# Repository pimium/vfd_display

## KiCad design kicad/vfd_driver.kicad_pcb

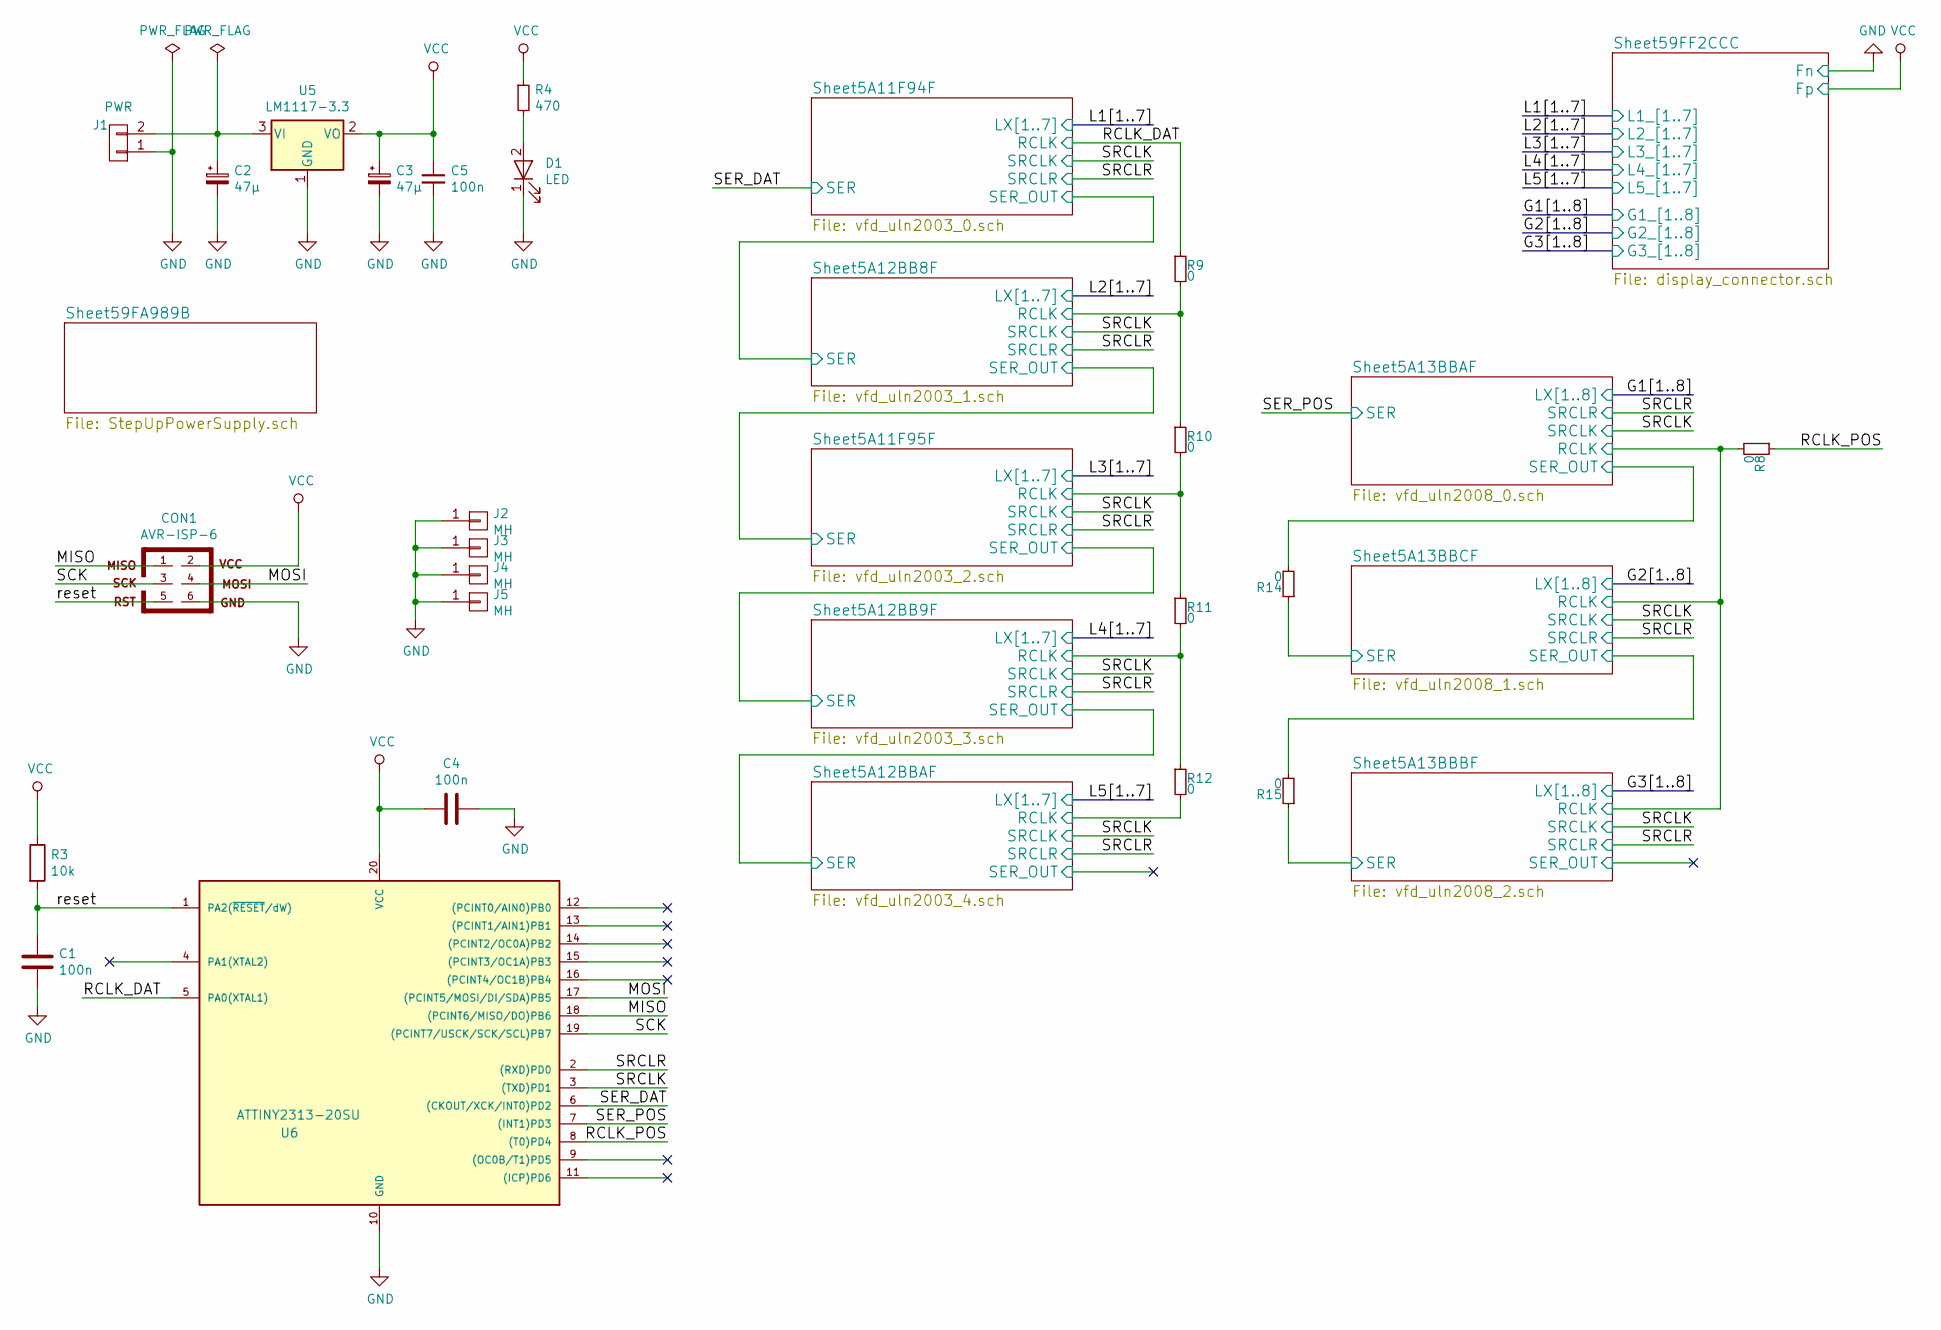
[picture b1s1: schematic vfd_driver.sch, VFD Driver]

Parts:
C1, C4, C5: 100n; C_0805_HandSoldering
C2, C3: 47µ; CP_Radial_Tantal_D4.5mm_P2.50mm
CON1: AVR-ISP-6; Pin_Header_Straight_2x03_Pitch2.54mm_SMD
D1: LED; LED_0805
J1: PWR; PINHEAD1-2
J2, J3, J4, J5: MH; MountingHole_3.2mm_M3_DIN965_Pad
R3: 10k; R_1206
R4: 470; R_1206
R8, R9, R10, R11, R12, R14, R15: 0; R_1206
U5: LM1117-3.3; SOT-223_pin4_3
U6: ATTINY2313-20SU; SOIC-20W_7.5x12.8mm_Pitch1.27mm

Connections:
/MISO: CON1.1, U6.18 ((PCINT6/MISO/DO)PB6)
/MOSI: CON1.4, U6.17 ((PCINT5/MOSI/DI/SDA)PB5)
/RCLK_0: R8.1, U6.8 ((T0)PD4)
/RCLK_7: R9.1, U6.5 (PA0(XTAL1)); also elsewhere on the board
/SCK: CON1.3, U6.19 ((PCINT7/USCK/SCK/SCL)PB7)
/SER_DAT: U6.6 ((CKOUT/XCK/INT0)PD2); also elsewhere on the board
/SER_POS: U6.7 ((INT1)PD3); also elsewhere on the board
/SRCLK: U6.3 ((TXD)PD1); also elsewhere on the board
/SRCLR: U6.2 ((RXD)PD0); also elsewhere on the board
/Sheet5A11F95F/RCLK: R10.2, R11.1; also elsewhere on the board
/Sheet5A12BB8F/RCLK: R9.2, R10.1; also elsewhere on the board
/Sheet5A12BB9F/RCLK: R11.2, R12.1; also elsewhere on the board
/Sheet5A12BBAF/RCLK: R12.2; also elsewhere on the board
/Sheet5A13BBAF/RCLK: R8.2; also elsewhere on the board
/Sheet5A13BBAF/SER_OUT: R14.2; also elsewhere on the board
/Sheet5A13BBBF/SER: R15.1; also elsewhere on the board
/Sheet5A13BBCF/SER: R14.1; also elsewhere on the board
/Sheet5A13BBCF/SER_OUT: R15.2; also elsewhere on the board
/reset: C1.1, CON1.5, R3.2, U6.1 (PA2(~RESET~/dW))
GND: C1.2, C2.2, C3.2, C4.1, C5.2, CON1.6, D1.1 (K), J1.1, J2.1, J3.1, J4.1, J5.1, U5.1 (GND), U6.10 (GND); also elsewhere on the board
unnamed: C2.1, J1.2, U5.3 (VI)
unnamed: D1.2 (A), R4.2
VCC: C3.1, C4.2, C5.1, CON1.2, R3.1, R4.1, U5.2 (VO), U6.20 (VCC); also elsewhere on the board

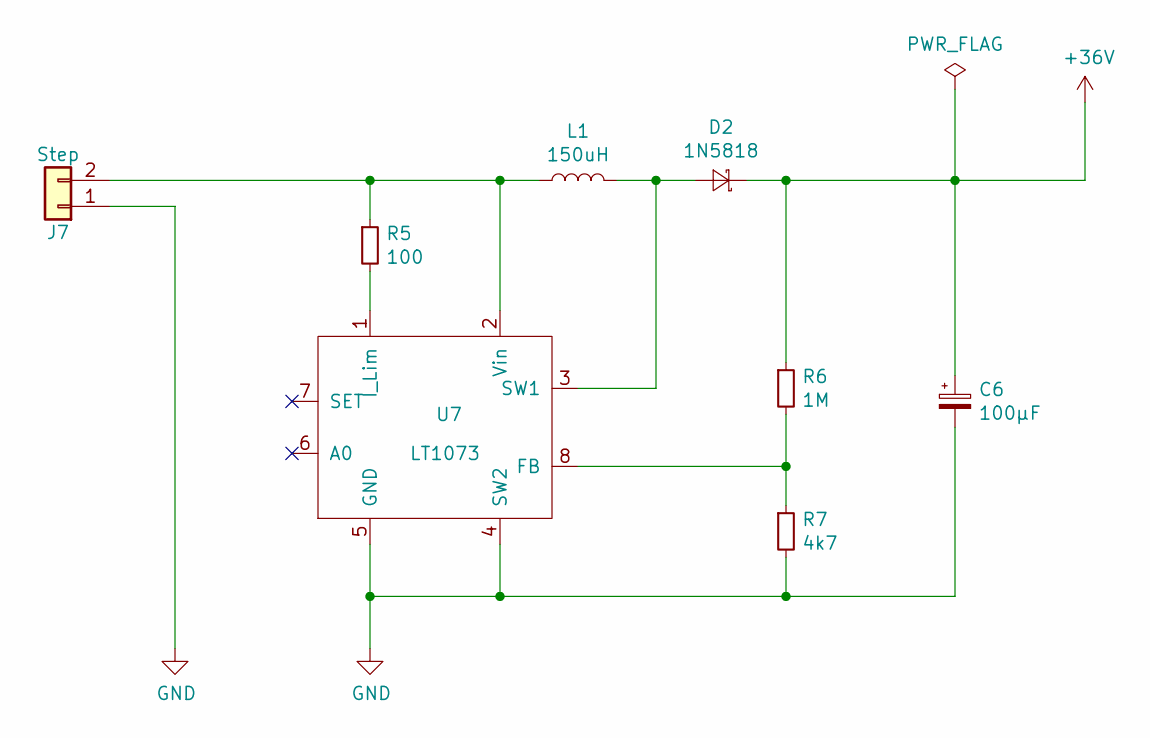
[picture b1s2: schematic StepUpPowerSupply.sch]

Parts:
C6: 100µF; CP_Elec_8x5.4
D2: 1N5818; D_SMA_Handsoldering
J7: Step; PINHEAD1-2
L1: 150uH; Choke_CD75
R5: 100; R_1206
R6: 1M; R_1206
R7: 4k7; R_1206
U7: LT1073; SOIC-8_3.9x4.9mm_Pitch1.27mm

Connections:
+36V: C6.1, D2.1 (K), R6.1; also elsewhere on the board
GND: C6.2, J7.1, R7.2, U7.4 (SW2), U7.5 (GND); also elsewhere on the board
unnamed: D2.2 (A), L1.2, U7.3 (SW1)
unnamed: J7.2, L1.1, R5.1, U7.2 (Vin)
unnamed: R5.2, U7.1 (I_Lim)
unnamed: R6.2, R7.1, U7.8 (FB)

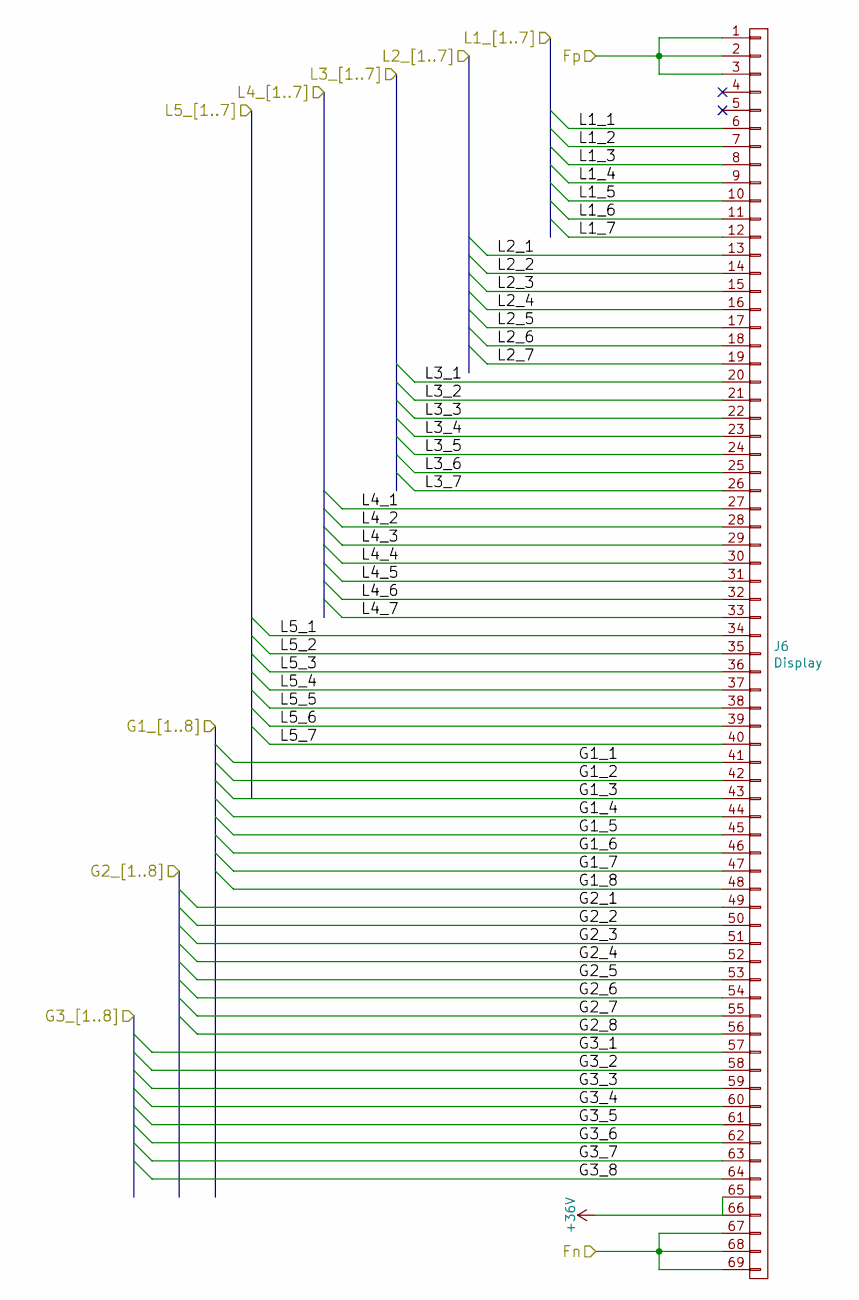
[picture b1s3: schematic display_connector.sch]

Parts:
J6: Display; vfd_FUTABA_24-SD-01GK_24x1

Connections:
+36V: J6.65, J6.66; also elsewhere on the board
/Sheet59FF2CCC/G1_1: J6.41; also elsewhere on the board
/Sheet59FF2CCC/G1_2: J6.42; also elsewhere on the board
/Sheet59FF2CCC/G1_3: J6.43; also elsewhere on the board
/Sheet59FF2CCC/G1_4: J6.44; also elsewhere on the board
/Sheet59FF2CCC/G1_5: J6.45; also elsewhere on the board
/Sheet59FF2CCC/G1_6: J6.46; also elsewhere on the board
/Sheet59FF2CCC/G1_7: J6.47; also elsewhere on the board
/Sheet59FF2CCC/G1_8: J6.48; also elsewhere on the board
/Sheet59FF2CCC/G2_1: J6.49; also elsewhere on the board
/Sheet59FF2CCC/G2_2: J6.50; also elsewhere on the board
/Sheet59FF2CCC/G2_3: J6.51; also elsewhere on the board
/Sheet59FF2CCC/G2_4: J6.52; also elsewhere on the board
/Sheet59FF2CCC/G2_5: J6.53; also elsewhere on the board
/Sheet59FF2CCC/G2_6: J6.54; also elsewhere on the board
/Sheet59FF2CCC/G2_7: J6.55; also elsewhere on the board
/Sheet59FF2CCC/G2_8: J6.56; also elsewhere on the board
/Sheet59FF2CCC/G3_1: J6.57; also elsewhere on the board
/Sheet59FF2CCC/G3_2: J6.58; also elsewhere on the board
/Sheet59FF2CCC/G3_3: J6.59; also elsewhere on the board
/Sheet59FF2CCC/G3_4: J6.60; also elsewhere on the board
/Sheet59FF2CCC/G3_5: J6.61; also elsewhere on the board
/Sheet59FF2CCC/G3_6: J6.62; also elsewhere on the board
/Sheet59FF2CCC/G3_7: J6.63; also elsewhere on the board
/Sheet59FF2CCC/G3_8: J6.64; also elsewhere on the board
/Sheet59FF2CCC/L1_1: J6.6; also elsewhere on the board
/Sheet59FF2CCC/L1_2: J6.7; also elsewhere on the board
/Sheet59FF2CCC/L1_3: J6.8; also elsewhere on the board
/Sheet59FF2CCC/L1_4: J6.9; also elsewhere on the board
/Sheet59FF2CCC/L1_5: J6.10; also elsewhere on the board
/Sheet59FF2CCC/L1_6: J6.11; also elsewhere on the board
/Sheet59FF2CCC/L1_7: J6.12; also elsewhere on the board
/Sheet59FF2CCC/L2_1: J6.13; also elsewhere on the board
/Sheet59FF2CCC/L2_2: J6.14; also elsewhere on the board
/Sheet59FF2CCC/L2_3: J6.15; also elsewhere on the board
/Sheet59FF2CCC/L2_4: J6.16; also elsewhere on the board
/Sheet59FF2CCC/L2_5: J6.17; also elsewhere on the board
/Sheet59FF2CCC/L2_6: J6.18; also elsewhere on the board
/Sheet59FF2CCC/L2_7: J6.19; also elsewhere on the board
/Sheet59FF2CCC/L3_1: J6.20; also elsewhere on the board
/Sheet59FF2CCC/L3_2: J6.21; also elsewhere on the board
/Sheet59FF2CCC/L3_3: J6.22; also elsewhere on the board
/Sheet59FF2CCC/L3_4: J6.23; also elsewhere on the board
/Sheet59FF2CCC/L3_5: J6.24; also elsewhere on the board
/Sheet59FF2CCC/L3_6: J6.25; also elsewhere on the board
/Sheet59FF2CCC/L3_7: J6.26; also elsewhere on the board
/Sheet59FF2CCC/L4_1: J6.27; also elsewhere on the board
/Sheet59FF2CCC/L4_2: J6.28; also elsewhere on the board
/Sheet59FF2CCC/L4_3: J6.29; also elsewhere on the board
/Sheet59FF2CCC/L4_4: J6.30; also elsewhere on the board
/Sheet59FF2CCC/L4_5: J6.31; also elsewhere on the board
/Sheet59FF2CCC/L4_6: J6.32; also elsewhere on the board
/Sheet59FF2CCC/L4_7: J6.33; also elsewhere on the board
/Sheet59FF2CCC/L5_1: J6.34; also elsewhere on the board
/Sheet59FF2CCC/L5_2: J6.35; also elsewhere on the board
/Sheet59FF2CCC/L5_3: J6.36; also elsewhere on the board
/Sheet59FF2CCC/L5_4: J6.37; also elsewhere on the board
/Sheet59FF2CCC/L5_5: J6.38; also elsewhere on the board
/Sheet59FF2CCC/L5_6: J6.39; also elsewhere on the board
/Sheet59FF2CCC/L5_7: J6.40; also elsewhere on the board
GND: J6.67, J6.68, J6.69; also elsewhere on the board
VCC: J6.1, J6.2, J6.3; also elsewhere on the board

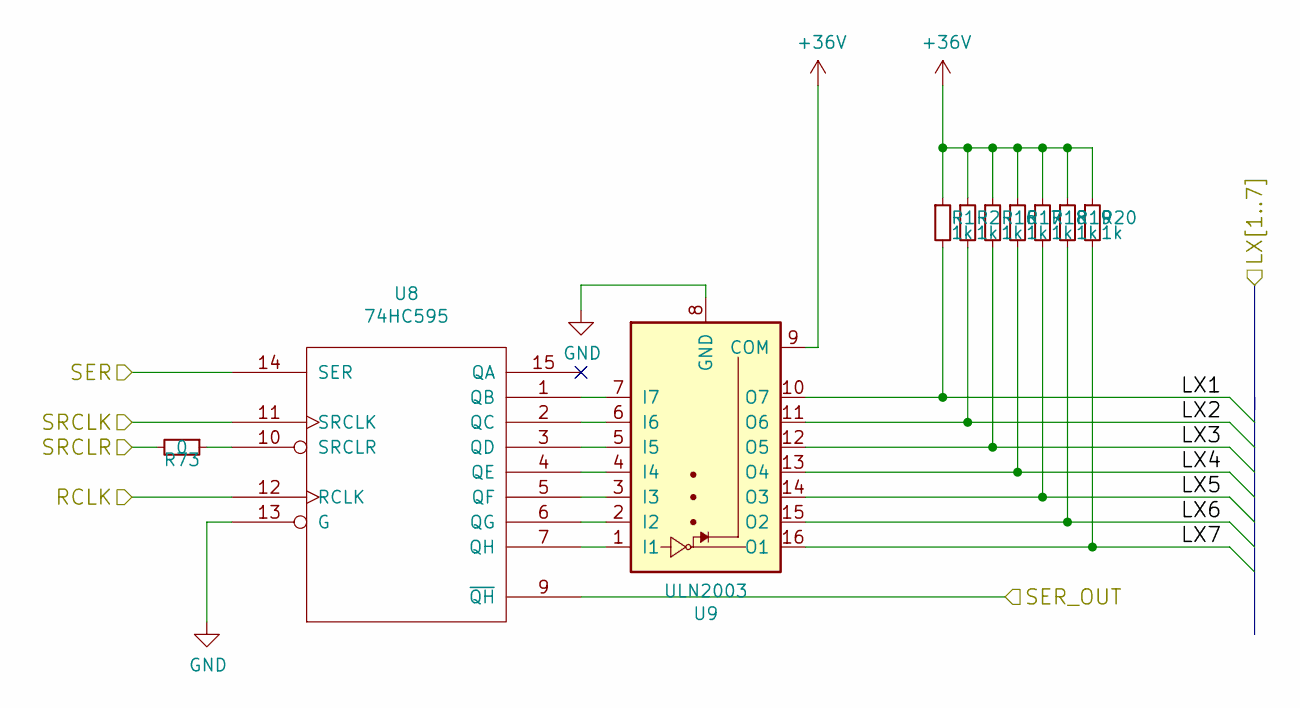
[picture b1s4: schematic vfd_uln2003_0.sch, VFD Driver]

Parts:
R1, R2: 1k; C_0805_HandSoldering
R16, R17, R18, R19, R20: 1k; R_0805_HandSoldering
R73: 0; R_1206
U8: 74HC595; SOIC-16_3.9x9.9mm_Pitch1.27mm
U9: ULN2003; SOIC-16_3.9x9.9mm_Pitch1.27mm

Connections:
+36V: R1.1, R2.1, R16.1, R17.1, R18.1, R19.1, R20.1, U9.9 (COM); also elsewhere on the board
/RCLK_7: U8.12 (RCLK); also elsewhere on the board
/SER_DAT: U8.14 (SER); also elsewhere on the board
/SRCLK: U8.11 (SRCLK); also elsewhere on the board
/SRCLR: R73.2; also elsewhere on the board
/Sheet5A12BB8F/SER: U8.9 (~QH); also elsewhere on the board
/Sheet59FF2CCC/L1_1: R1.2, U9.10 (O7); also elsewhere on the board
/Sheet59FF2CCC/L1_2: R2.2, U9.11 (O6); also elsewhere on the board
/Sheet59FF2CCC/L1_3: R16.2, U9.12 (O5); also elsewhere on the board
/Sheet59FF2CCC/L1_4: R17.2, U9.13 (O4); also elsewhere on the board
/Sheet59FF2CCC/L1_5: R18.2, U9.14 (O3); also elsewhere on the board
/Sheet59FF2CCC/L1_6: R19.2, U9.15 (O2); also elsewhere on the board
/Sheet59FF2CCC/L1_7: R20.2, U9.16 (O1); also elsewhere on the board
GND: U8.8 (GND), U8.13 (G), U9.8 (GND); also elsewhere on the board
unnamed: R73.1, U8.10 (SRCLR)
unnamed: U8.1 (QB), U9.7 (I7)
unnamed: U8.2 (QC), U9.6 (I6)
unnamed: U8.3 (QD), U9.5 (I5)
unnamed: U8.4 (QE), U9.4 (I4)
unnamed: U8.5 (QF), U9.3 (I3)
unnamed: U8.6 (QG), U9.2 (I2)
unnamed: U8.7 (QH), U9.1 (I1)
VCC: U8.16 (VCC); also elsewhere on the board

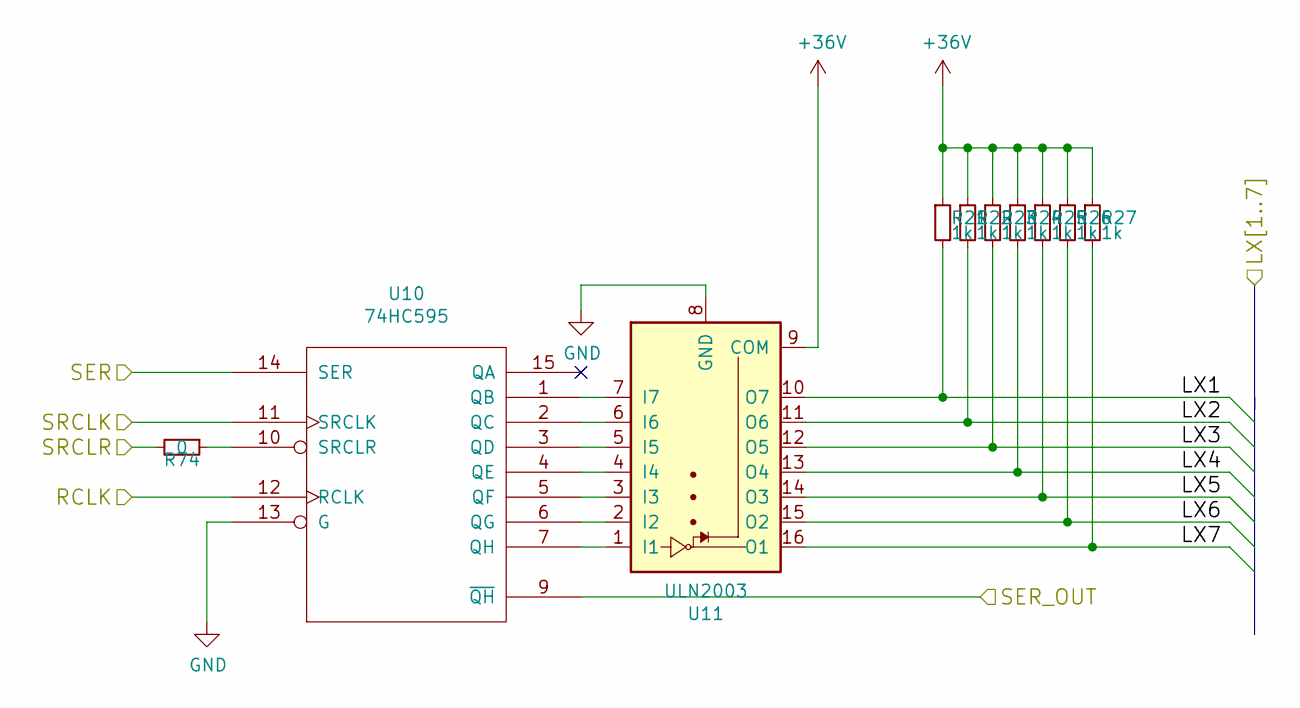
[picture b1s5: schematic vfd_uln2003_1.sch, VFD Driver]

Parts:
R21, R22, R23, R24, R25, R26, R27: 1k; R_0805_HandSoldering
R74: 0; R_1206
U10: 74HC595; SOIC-16_3.9x9.9mm_Pitch1.27mm
U11: ULN2003; SOIC-16_3.9x9.9mm_Pitch1.27mm

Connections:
+36V: R21.1, R22.1, R23.1, R24.1, R25.1, R26.1, R27.1, U11.9 (COM); also elsewhere on the board
/SRCLK: U10.11 (SRCLK); also elsewhere on the board
/SRCLR: R74.2; also elsewhere on the board
/Sheet5A11F95F/SER: U10.9 (~QH); also elsewhere on the board
/Sheet5A12BB8F/RCLK: U10.12 (RCLK); also elsewhere on the board
/Sheet5A12BB8F/SER: U10.14 (SER); also elsewhere on the board
/Sheet59FF2CCC/L2_1: R21.2, U11.10 (O7); also elsewhere on the board
/Sheet59FF2CCC/L2_2: R22.2, U11.11 (O6); also elsewhere on the board
/Sheet59FF2CCC/L2_3: R23.2, U11.12 (O5); also elsewhere on the board
/Sheet59FF2CCC/L2_4: R24.2, U11.13 (O4); also elsewhere on the board
/Sheet59FF2CCC/L2_5: R25.2, U11.14 (O3); also elsewhere on the board
/Sheet59FF2CCC/L2_6: R26.2, U11.15 (O2); also elsewhere on the board
/Sheet59FF2CCC/L2_7: R27.2, U11.16 (O1); also elsewhere on the board
GND: U10.8 (GND), U10.13 (G), U11.8 (GND); also elsewhere on the board
unnamed: R74.1, U10.10 (SRCLR)
unnamed: U10.1 (QB), U11.7 (I7)
unnamed: U10.2 (QC), U11.6 (I6)
unnamed: U10.3 (QD), U11.5 (I5)
unnamed: U10.4 (QE), U11.4 (I4)
unnamed: U10.5 (QF), U11.3 (I3)
unnamed: U10.6 (QG), U11.2 (I2)
unnamed: U10.7 (QH), U11.1 (I1)
VCC: U10.16 (VCC); also elsewhere on the board

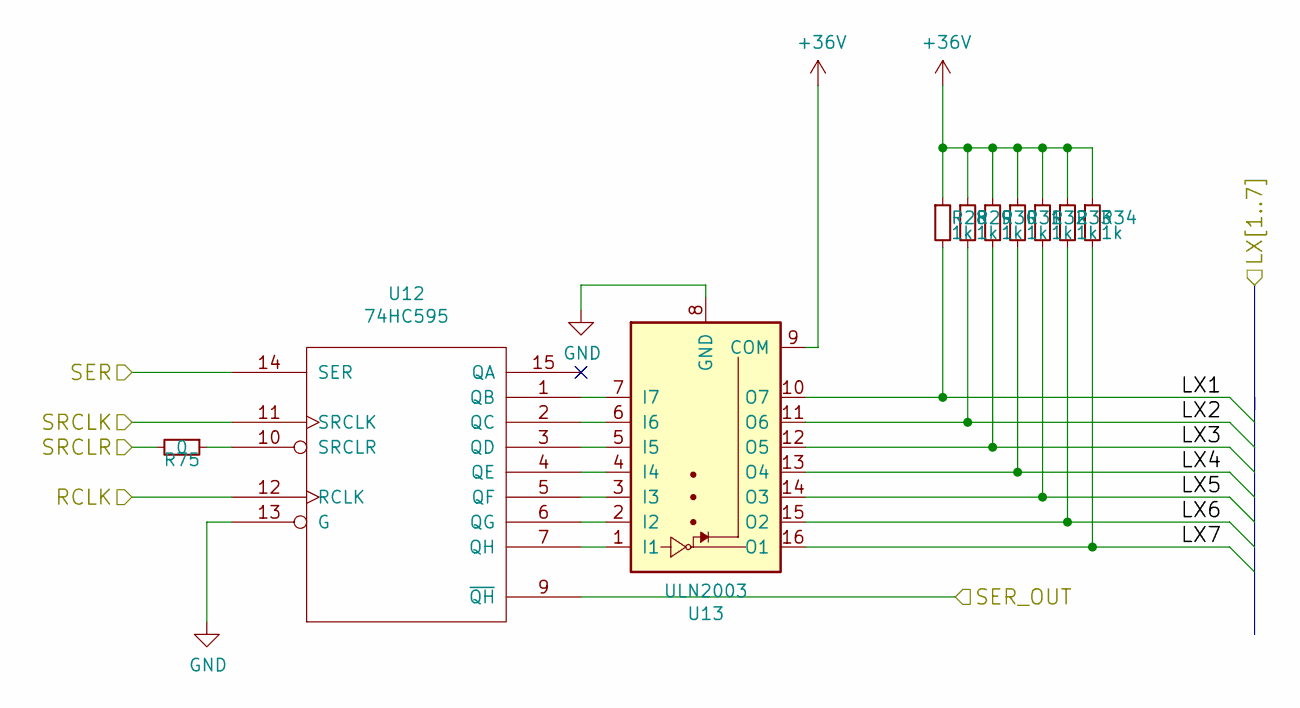
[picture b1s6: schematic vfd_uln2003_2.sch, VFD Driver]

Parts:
R28, R29, R30, R31, R32, R33, R34: 1k; R_0805_HandSoldering
R75: 0; R_1206
U12: 74HC595; SOIC-16_3.9x9.9mm_Pitch1.27mm
U13: ULN2003; SOIC-16_3.9x9.9mm_Pitch1.27mm

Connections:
+36V: R28.1, R29.1, R30.1, R31.1, R32.1, R33.1, R34.1, U13.9 (COM); also elsewhere on the board
/SRCLK: U12.11 (SRCLK); also elsewhere on the board
/SRCLR: R75.2; also elsewhere on the board
/Sheet5A11F95F/RCLK: U12.12 (RCLK); also elsewhere on the board
/Sheet5A11F95F/SER: U12.14 (SER); also elsewhere on the board
/Sheet5A12BB9F/SER: U12.9 (~QH); also elsewhere on the board
/Sheet59FF2CCC/L3_1: R28.2, U13.10 (O7); also elsewhere on the board
/Sheet59FF2CCC/L3_2: R29.2, U13.11 (O6); also elsewhere on the board
/Sheet59FF2CCC/L3_3: R30.2, U13.12 (O5); also elsewhere on the board
/Sheet59FF2CCC/L3_4: R31.2, U13.13 (O4); also elsewhere on the board
/Sheet59FF2CCC/L3_5: R32.2, U13.14 (O3); also elsewhere on the board
/Sheet59FF2CCC/L3_6: R33.2, U13.15 (O2); also elsewhere on the board
/Sheet59FF2CCC/L3_7: R34.2, U13.16 (O1); also elsewhere on the board
GND: U12.8 (GND), U12.13 (G), U13.8 (GND); also elsewhere on the board
unnamed: R75.1, U12.10 (SRCLR)
unnamed: U12.1 (QB), U13.7 (I7)
unnamed: U12.2 (QC), U13.6 (I6)
unnamed: U12.3 (QD), U13.5 (I5)
unnamed: U12.4 (QE), U13.4 (I4)
unnamed: U12.5 (QF), U13.3 (I3)
unnamed: U12.6 (QG), U13.2 (I2)
unnamed: U12.7 (QH), U13.1 (I1)
VCC: U12.16 (VCC); also elsewhere on the board

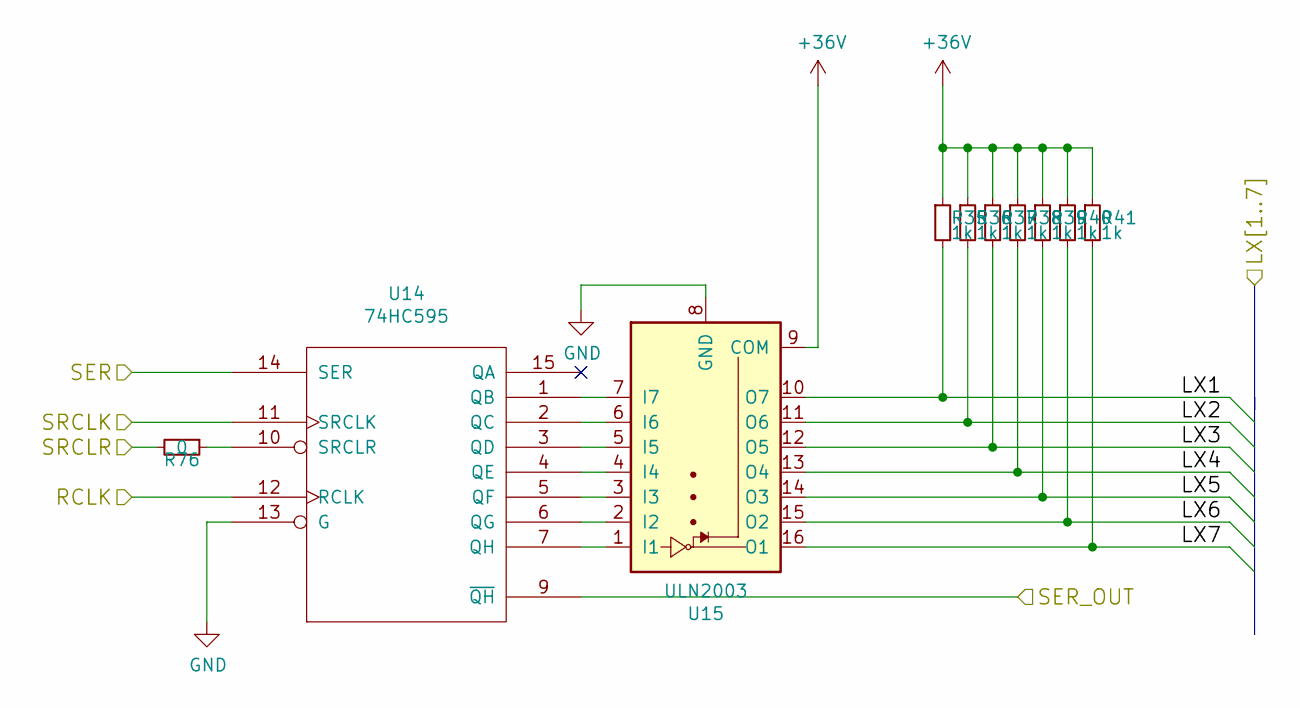
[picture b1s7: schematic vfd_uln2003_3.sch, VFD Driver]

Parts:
R35, R36, R37, R38, R39, R40, R41: 1k; R_0805_HandSoldering
R76: 0; R_1206
U14: 74HC595; SOIC-16_3.9x9.9mm_Pitch1.27mm
U15: ULN2003; SOIC-16_3.9x9.9mm_Pitch1.27mm

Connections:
+36V: R35.1, R36.1, R37.1, R38.1, R39.1, R40.1, R41.1, U15.9 (COM); also elsewhere on the board
/SRCLK: U14.11 (SRCLK); also elsewhere on the board
/SRCLR: R76.2; also elsewhere on the board
/Sheet5A12BB9F/RCLK: U14.12 (RCLK); also elsewhere on the board
/Sheet5A12BB9F/SER: U14.14 (SER); also elsewhere on the board
/Sheet5A12BBAF/SER: U14.9 (~QH); also elsewhere on the board
/Sheet59FF2CCC/L4_1: R35.2, U15.10 (O7); also elsewhere on the board
/Sheet59FF2CCC/L4_2: R36.2, U15.11 (O6); also elsewhere on the board
/Sheet59FF2CCC/L4_3: R37.2, U15.12 (O5); also elsewhere on the board
/Sheet59FF2CCC/L4_4: R38.2, U15.13 (O4); also elsewhere on the board
/Sheet59FF2CCC/L4_5: R39.2, U15.14 (O3); also elsewhere on the board
/Sheet59FF2CCC/L4_6: R40.2, U15.15 (O2); also elsewhere on the board
/Sheet59FF2CCC/L4_7: R41.2, U15.16 (O1); also elsewhere on the board
GND: U14.8 (GND), U14.13 (G), U15.8 (GND); also elsewhere on the board
unnamed: R76.1, U14.10 (SRCLR)
unnamed: U14.1 (QB), U15.7 (I7)
unnamed: U14.2 (QC), U15.6 (I6)
unnamed: U14.3 (QD), U15.5 (I5)
unnamed: U14.4 (QE), U15.4 (I4)
unnamed: U14.5 (QF), U15.3 (I3)
unnamed: U14.6 (QG), U15.2 (I2)
unnamed: U14.7 (QH), U15.1 (I1)
VCC: U14.16 (VCC); also elsewhere on the board

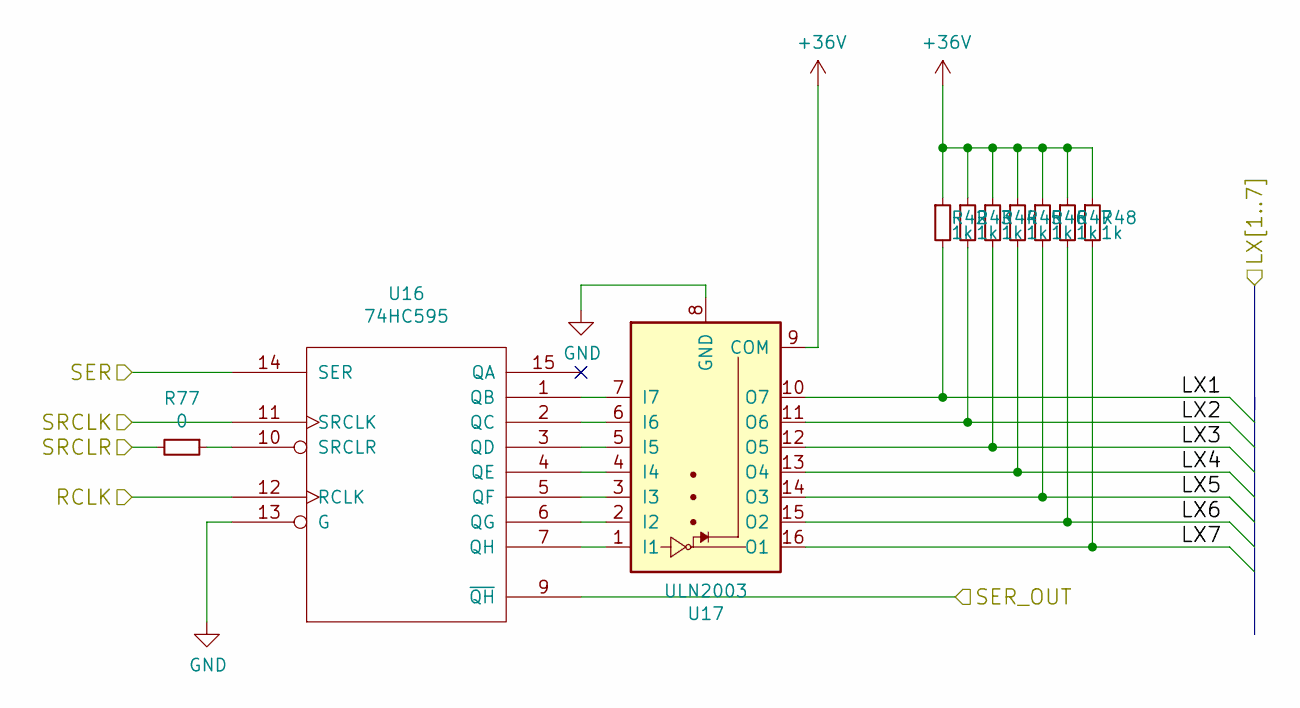
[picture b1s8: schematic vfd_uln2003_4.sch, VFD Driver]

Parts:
R42, R43, R44, R45, R46, R47, R48: 1k; R_0805_HandSoldering
R77: 0; R_1206
U16: 74HC595; SOIC-16_3.9x9.9mm_Pitch1.27mm
U17: ULN2003; SOIC-16_3.9x9.9mm_Pitch1.27mm

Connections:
+36V: R42.1, R43.1, R44.1, R45.1, R46.1, R47.1, R48.1, U17.9 (COM); also elsewhere on the board
/SRCLK: U16.11 (SRCLK); also elsewhere on the board
/SRCLR: R77.2; also elsewhere on the board
/Sheet5A12BBAF/RCLK: U16.12 (RCLK); also elsewhere on the board
/Sheet5A12BBAF/SER: U16.14 (SER); also elsewhere on the board
/Sheet59FF2CCC/L5_1: R42.2, U17.10 (O7); also elsewhere on the board
/Sheet59FF2CCC/L5_2: R43.2, U17.11 (O6); also elsewhere on the board
/Sheet59FF2CCC/L5_3: R44.2, U17.12 (O5); also elsewhere on the board
/Sheet59FF2CCC/L5_4: R45.2, U17.13 (O4); also elsewhere on the board
/Sheet59FF2CCC/L5_5: R46.2, U17.14 (O3); also elsewhere on the board
/Sheet59FF2CCC/L5_6: R47.2, U17.15 (O2); also elsewhere on the board
/Sheet59FF2CCC/L5_7: R48.2, U17.16 (O1); also elsewhere on the board
GND: U16.8 (GND), U16.13 (G), U17.8 (GND); also elsewhere on the board
unnamed: R77.1, U16.10 (SRCLR)
unnamed: U16.1 (QB), U17.7 (I7)
unnamed: U16.2 (QC), U17.6 (I6)
unnamed: U16.3 (QD), U17.5 (I5)
unnamed: U16.4 (QE), U17.4 (I4)
unnamed: U16.5 (QF), U17.3 (I3)
unnamed: U16.6 (QG), U17.2 (I2)
unnamed: U16.7 (QH), U17.1 (I1)
VCC: U16.16 (VCC); also elsewhere on the board

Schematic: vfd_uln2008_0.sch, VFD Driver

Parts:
R13, R78: 0; R_1206
R49, R50, R51, R52, R53, R54, R55, R56: 1k; R_0805_HandSoldering
U18: 74HC595; SOIC-16_3.9x9.9mm_Pitch1.27mm
U19: ULN2803A; SOIC-18W_7.5x11.6mm_Pitch1.27mm

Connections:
+36V: R49.1, R50.1, R51.1, R52.1, R53.1, R54.1, R55.1, R56.1, U19.10 (COM); also elsewhere on the board
/SER_POS: R13.2; also elsewhere on the board
/SRCLK: U18.11 (SRCLK); also elsewhere on the board
/SRCLR: R78.2; also elsewhere on the board
/Sheet5A13BBAF/RCLK: U18.12 (RCLK); also elsewhere on the board
/Sheet5A13BBAF/SER_OUT: U18.9 (~QH); also elsewhere on the board
/Sheet59FF2CCC/G1_1: R49.2, U19.11 (O8); also elsewhere on the board
/Sheet59FF2CCC/G1_2: R50.2, U19.12 (O7); also elsewhere on the board
/Sheet59FF2CCC/G1_3: R51.2, U19.13 (O6); also elsewhere on the board
/Sheet59FF2CCC/G1_4: R52.2, U19.14 (O5); also elsewhere on the board
/Sheet59FF2CCC/G1_5: R53.2, U19.15 (O4); also elsewhere on the board
/Sheet59FF2CCC/G1_6: R54.2, U19.16 (O3); also elsewhere on the board
/Sheet59FF2CCC/G1_7: R55.2, U19.17 (O2); also elsewhere on the board
/Sheet59FF2CCC/G1_8: R56.2, U19.18 (O1); also elsewhere on the board
GND: U18.8 (GND), U18.13 (G), U19.9 (GND); also elsewhere on the board
unnamed: R13.1, U18.14 (SER)
unnamed: R78.1, U18.10 (SRCLR)
unnamed: U18.1 (QB), U19.7 (I7)
unnamed: U18.2 (QC), U19.6 (I6)
unnamed: U18.3 (QD), U19.5 (I5)
unnamed: U18.4 (QE), U19.4 (I4)
unnamed: U18.5 (QF), U19.3 (I3)
unnamed: U18.6 (QG), U19.2 (I2)
unnamed: U18.7 (QH), U19.1 (I1)
unnamed: U18.15 (QA), U19.8 (I8)
VCC: U18.16 (VCC); also elsewhere on the board

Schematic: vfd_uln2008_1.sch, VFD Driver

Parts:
R57, R58, R59, R60, R61, R62, R63, R64: 1k; R_0805_HandSoldering
R79, R80: 0; R_1206
U20: 74HC595; SOIC-16_3.9x9.9mm_Pitch1.27mm
U21: ULN2803A; SOIC-18W_7.5x11.6mm_Pitch1.27mm

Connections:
+36V: R57.1, R58.1, R59.1, R60.1, R61.1, R62.1, R63.1, R64.1, U21.10 (COM); also elsewhere on the board
/SRCLK: U20.11 (SRCLK); also elsewhere on the board
/SRCLR: R79.2; also elsewhere on the board
/Sheet5A13BBAF/RCLK: R80.2; also elsewhere on the board
/Sheet5A13BBCF/SER: U20.14 (SER); also elsewhere on the board
/Sheet5A13BBCF/SER_OUT: U20.9 (~QH); also elsewhere on the board
/Sheet59FF2CCC/G2_1: R57.2, U21.11 (O8); also elsewhere on the board
/Sheet59FF2CCC/G2_2: R58.2, U21.12 (O7); also elsewhere on the board
/Sheet59FF2CCC/G2_3: R59.2, U21.13 (O6); also elsewhere on the board
/Sheet59FF2CCC/G2_4: R60.2, U21.14 (O5); also elsewhere on the board
/Sheet59FF2CCC/G2_5: R61.2, U21.15 (O4); also elsewhere on the board
/Sheet59FF2CCC/G2_6: R62.2, U21.16 (O3); also elsewhere on the board
/Sheet59FF2CCC/G2_7: R63.2, U21.17 (O2); also elsewhere on the board
/Sheet59FF2CCC/G2_8: R64.2, U21.18 (O1); also elsewhere on the board
GND: U20.8 (GND), U20.13 (G), U21.9 (GND); also elsewhere on the board
unnamed: R79.1, U20.10 (SRCLR)
unnamed: R80.1, U20.12 (RCLK)
unnamed: U20.1 (QB), U21.7 (I7)
unnamed: U20.2 (QC), U21.6 (I6)
unnamed: U20.3 (QD), U21.5 (I5)
unnamed: U20.4 (QE), U21.4 (I4)
unnamed: U20.5 (QF), U21.3 (I3)
unnamed: U20.6 (QG), U21.2 (I2)
unnamed: U20.7 (QH), U21.1 (I1)
unnamed: U20.15 (QA), U21.8 (I8)
VCC: U20.16 (VCC); also elsewhere on the board

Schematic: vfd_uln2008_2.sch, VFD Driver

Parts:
R65, R66, R67, R68, R69, R70, R71, R72: 1k; R_0805_HandSoldering
U22: 74HC595; SOIC-16_3.9x9.9mm_Pitch1.27mm
U23: ULN2803A; SOIC-18W_7.5x11.6mm_Pitch1.27mm

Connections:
+36V: R65.1, R66.1, R67.1, R68.1, R69.1, R70.1, R71.1, R72.1, U23.10 (COM); also elsewhere on the board
/SRCLK: U22.11 (SRCLK); also elsewhere on the board
/SRCLR: U22.10 (SRCLR); also elsewhere on the board
/Sheet5A13BBAF/RCLK: U22.12 (RCLK); also elsewhere on the board
/Sheet5A13BBBF/SER: U22.14 (SER); also elsewhere on the board
/Sheet59FF2CCC/G3_1: R65.2, U23.11 (O8); also elsewhere on the board
/Sheet59FF2CCC/G3_2: R66.2, U23.12 (O7); also elsewhere on the board
/Sheet59FF2CCC/G3_3: R67.2, U23.13 (O6); also elsewhere on the board
/Sheet59FF2CCC/G3_4: R68.2, U23.14 (O5); also elsewhere on the board
/Sheet59FF2CCC/G3_5: R69.2, U23.15 (O4); also elsewhere on the board
/Sheet59FF2CCC/G3_6: R70.2, U23.16 (O3); also elsewhere on the board
/Sheet59FF2CCC/G3_7: R71.2, U23.17 (O2); also elsewhere on the board
/Sheet59FF2CCC/G3_8: R72.2, U23.18 (O1); also elsewhere on the board
GND: U22.8 (GND), U22.13 (G), U23.9 (GND); also elsewhere on the board
unnamed: U22.1 (QB), U23.7 (I7)
unnamed: U22.2 (QC), U23.6 (I6)
unnamed: U22.3 (QD), U23.5 (I5)
unnamed: U22.4 (QE), U23.4 (I4)
unnamed: U22.5 (QF), U23.3 (I3)
unnamed: U22.6 (QG), U23.2 (I2)
unnamed: U22.7 (QH), U23.1 (I1)
unnamed: U22.15 (QA), U23.8 (I8)
VCC: U22.16 (VCC); also elsewhere on the board

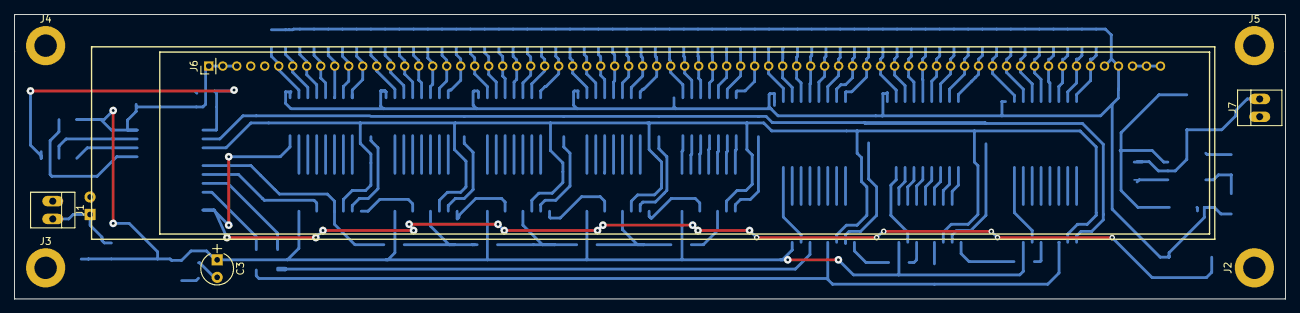
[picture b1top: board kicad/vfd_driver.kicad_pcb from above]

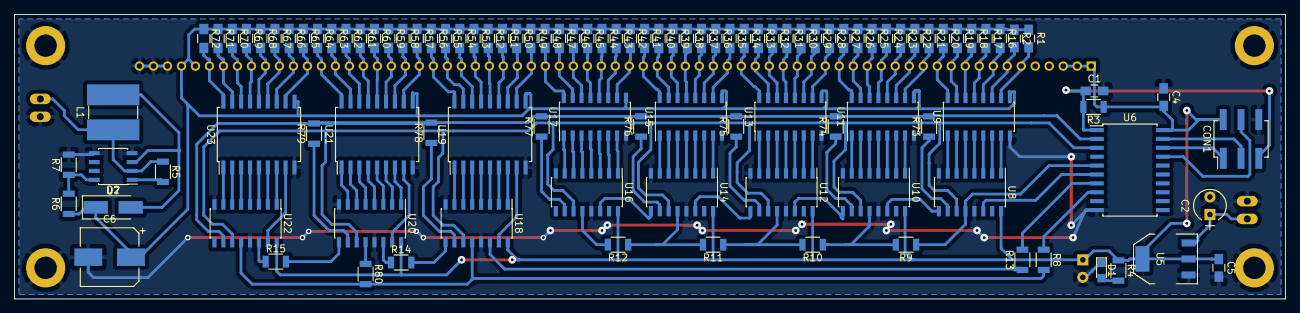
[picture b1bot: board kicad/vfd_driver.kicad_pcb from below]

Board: 2 copper layers, 181.6 x 40.6 mm, 116 parts (108 on the bottom side), 159 nets.
